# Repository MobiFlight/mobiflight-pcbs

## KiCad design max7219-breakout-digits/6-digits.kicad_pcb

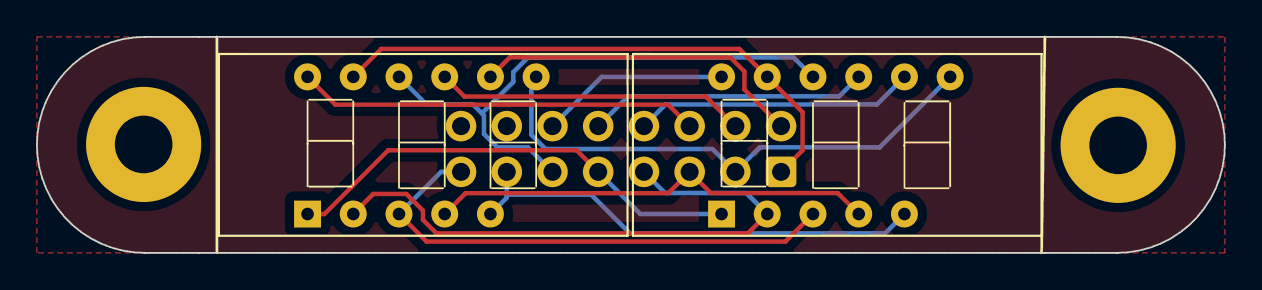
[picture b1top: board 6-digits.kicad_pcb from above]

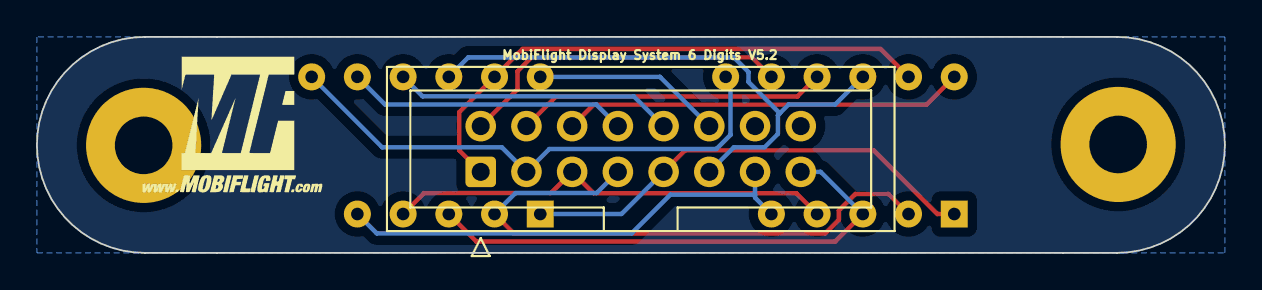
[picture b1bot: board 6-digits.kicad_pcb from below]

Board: 2 copper layers, 66.0 x 12.0 mm, 6 parts (2 on the bottom side), 14 nets.

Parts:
G2: LOGO; MobiFlight-Logo-Small
H1, H2: MountingHole 3.2mm; MountingHole_3.2mm_M3_Pad
J1: Conn_02x08_Odd_Even; IDC-Header_2x08_P2.54mm_Vertical
U1, U2: 7Segment 3 digit CC_STH; STH_7_3 Digits_0.28_CC

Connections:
/A: J1.1, U1.11 (a), U2.11 (a)
/B: J1.3, U1.7 (b), U2.7 (b)
/C: J1.5, U1.4 (c), U2.4 (c)
/D: J1.7, U1.2 (d), U2.2 (d)
/DIG0: J1.2, U2.8 (CC3)
/DIG1: J1.4, U2.9 (CC2)
/DIG2: J1.6, U2.12 (CC1)
/DIG3: J1.8, U1.8 (CC3)
/DIG4: J1.10, U1.9 (CC2)
/DIG5: J1.12, U1.12 (CC1)
/DP: J1.15, U1.3 (DPX), U2.3 (DPX)
/E: J1.9, U1.1 (e), U2.1 (e)
/F: J1.11, U1.10 (f), U2.10 (f)
/G: J1.13, U1.5 (g), U2.5 (g)

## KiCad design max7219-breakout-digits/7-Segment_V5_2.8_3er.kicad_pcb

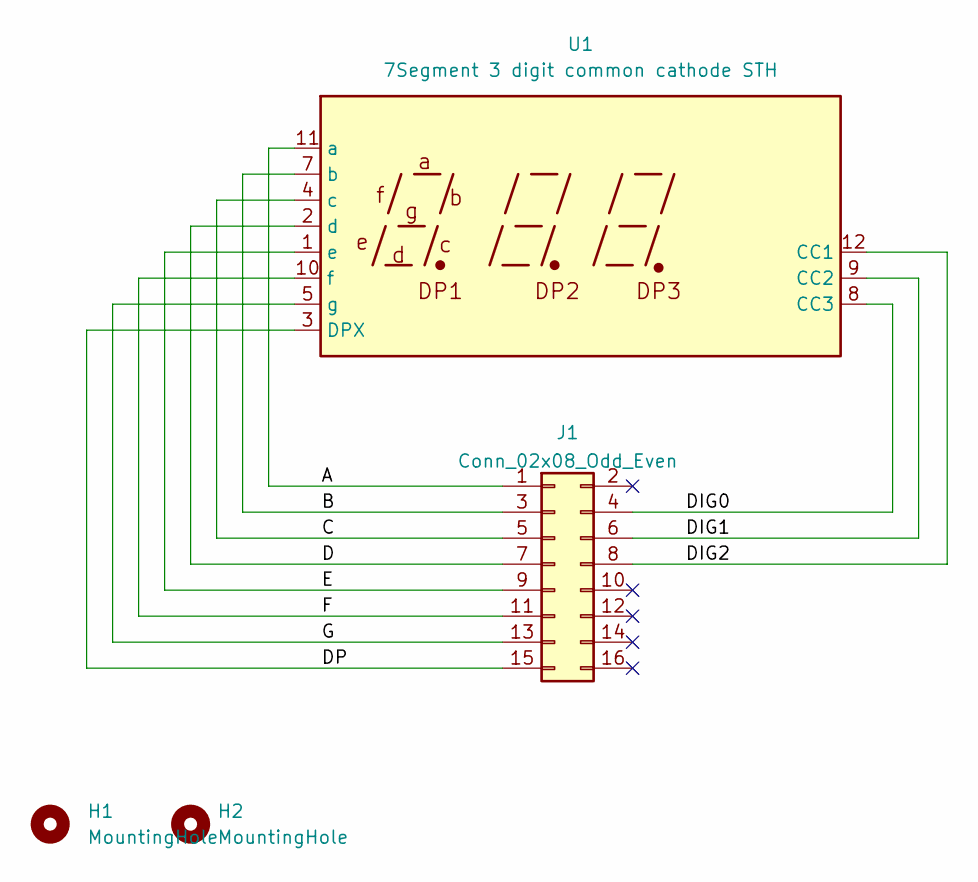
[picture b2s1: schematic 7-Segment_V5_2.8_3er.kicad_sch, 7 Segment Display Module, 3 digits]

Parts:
H1, H2: MountingHole; MountingHole_3.2mm_M3_Pad
J1: Conn_02x08_Odd_Even; IDC-Header_2x08_P2.54mm_Vertical
U1: 7Segment 3 digit common cathode STH; STH_7_3 Digits_0.28_CC

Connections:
/A: J1.1, U1.11 (a)
/B: J1.3, U1.7 (b)
/C: J1.5, U1.4 (c)
/D: J1.7, U1.2 (d)
/DIG0: J1.4, U1.8 (CC3)
/DIG1: J1.6, U1.9 (CC2)
/DIG2: J1.8, U1.12 (CC1)
/DP: J1.15, U1.3 (DPX)
/E: J1.9, U1.1 (e)
/F: J1.11, U1.10 (f)
/G: J1.13, U1.5 (g)

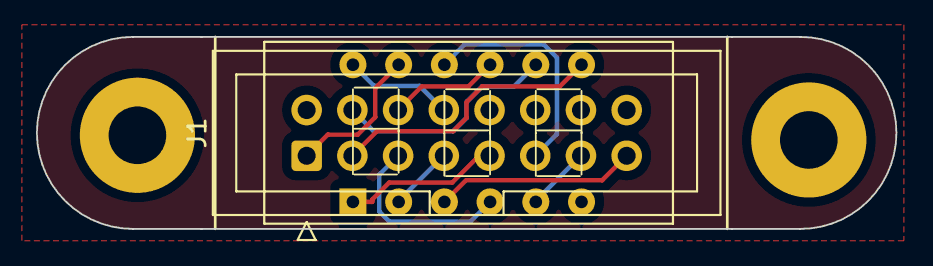
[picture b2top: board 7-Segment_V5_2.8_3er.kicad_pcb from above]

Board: 2 copper layers, 47.8 x 10.7 mm, 5 parts (1 on the bottom side), 11 nets.

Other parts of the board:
G2: LOGO; MobiFlight-Logo-Small

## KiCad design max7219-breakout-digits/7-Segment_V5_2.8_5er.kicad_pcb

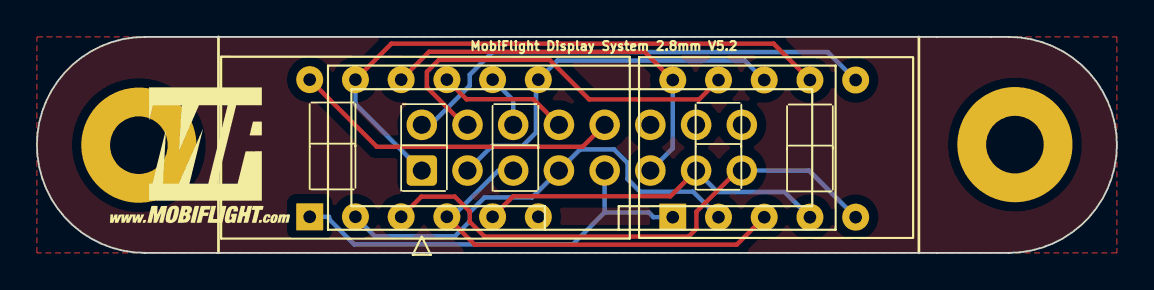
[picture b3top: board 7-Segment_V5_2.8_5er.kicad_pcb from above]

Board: 2 copper layers, 60.0 x 12.0 mm, 6 parts (0 on the bottom side), 13 nets.

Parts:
G2: LOGO; MobiFlight-Logo-Small
H1, H2: MountingHole 3.2mm; MountingHole_3.2mm_M3_Pad
J1: Conn_02x08_Odd_Even; IDC-Header_2x08_P2.54mm_Vertical
U1: 7Segment 3 digit CC_STH; STH_7_3 Digits_0.28_CC
U2: HDSM-443B_CC_2Digit_7Segment_STH; STH_7_2 Digits_0.28_CC

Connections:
/A: J1.1, U1.11 (a), U2.7 (A)
/B: J1.3, U1.7 (b), U2.8 (B)
/C: J1.5, U1.4 (c), U2.3 (C)
/D: J1.7, U1.2 (d), U2.2 (D)
/DIG0: J1.2, U2.6 (CC_DIG2)
/DIG1: J1.4, U2.9 (CC_DIG1)
/DIG2: J1.6, U1.8 (CC3)
/DIG3: J1.8, U1.9 (CC2)
/DIG4: J1.10, U1.12 (CC1)
/DP: J1.15, U1.3 (DPX), U2.5 (DP)
/E: J1.9, U1.1 (e), U2.1 (E)
/F: J1.11, U1.10 (f), U2.10 (F)
/G: J1.13, U1.5 (g), U2.4 (G)
